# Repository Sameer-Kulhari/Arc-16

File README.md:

# Arc-16

Arc-16 is a macro-pad with 16 keys,oled and rgb for aesthetics and look ,with a custom cool looking 3d case and working on kmk firmware .

## Features :
- 16 keys 
- Oled (128*32)
- Rgb under keys 
- kmk firmware
- 3 layers for rgb and functions control keys

## CAD :
#### Here are some looks of Arc-16 .

It has two parts top and bottom which can be assembled using M3 screws and heatsets.The design is made in Onshape.

### Full Case 

### Bottom

## PCB :
#### Here are some looks of PCB

This pcb is made in kicad.
### 3d view

### Schematics

## Firmware 
### Arc -16 uses kmk Firmware with Circuit-python

- 3 layers for more keys
- Oled displays current layer
- Rgb with different modes

## BOM 
Here is a list of materials required to make the Arc-16

- 1x Seeed XIAO RP2040
- 16x Cherry MX 1.0u Switches
- 1x 0.91 inch OLED display
- 9x SK6812 mini-e LEDs
- 16x 1N14148 diodes
- Pcb of Arc-16
- Case of Arc-16
- 4x M3 screws
- 4x M3 heatsets
- 16x Blank DSA keycaps

## Extra 

### All images are attached in each section along with dependancies.Have a look at it.
####  _________________Thank You!____________________

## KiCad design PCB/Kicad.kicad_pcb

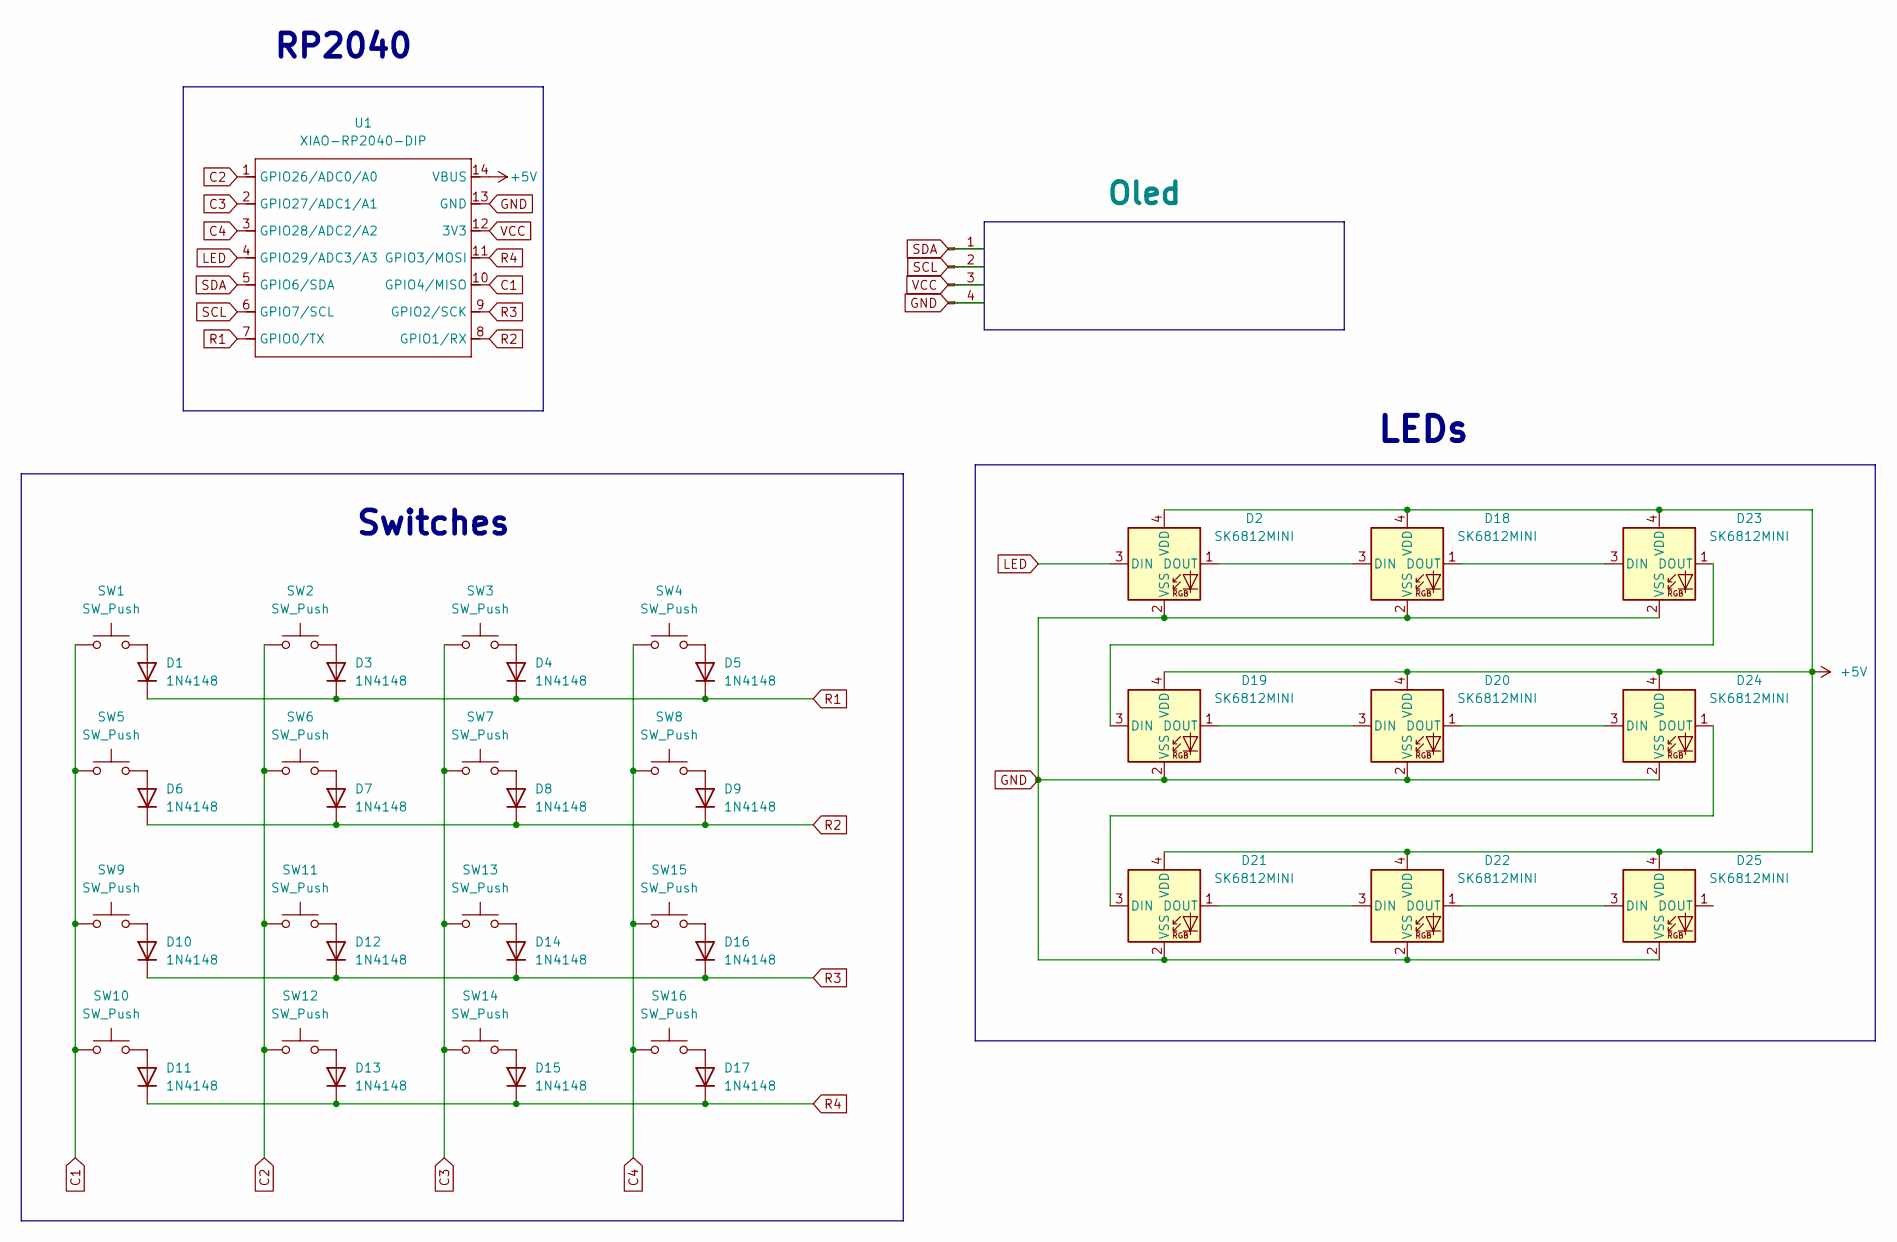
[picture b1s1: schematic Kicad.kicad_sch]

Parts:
D1, D3, D4, D5, D6, D7, D8, D9, D10, D11, D12, D13, D14, D15, D16, D17: 1N4148; D_DO-35_SOD27_P7.62mm_Horizontal
D2, D18, D19, D20, D21, D22, D23, D24, D25: SK6812MINI; SK6812-MINI-E
J1: Oled; PinHeader_1x04_P2.54mm_Vertical
SW1, SW2, SW3, SW4, SW5, SW6, SW7, SW8, SW9, SW10, SW11, SW12, SW13, SW14, SW15, SW16: SW_Push; SW_Cherry_MX_1.00u_PCB_With_3d
U1: XIAO-RP2040-DIP

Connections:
+5V: D2.4 (VDD), D18.4 (VDD), D19.4 (VDD), D20.4 (VDD), D21.4 (VDD), D22.4 (VDD), D23.4 (VDD), D24.4 (VDD), D25.4 (VDD), U1.14 (VBUS)
C1: SW1.1, SW5.1, SW9.1, SW10.1, U1.10 (GPIO4/MISO)
C2: SW2.1, SW6.1, SW11.1, SW12.1, U1.1 (GPIO26/ADC0/A0)
C3: SW3.1, SW7.1, SW13.1, SW14.1, U1.2 (GPIO27/ADC1/A1)
C4: SW4.1, SW8.1, SW15.1, SW16.1, U1.3 (GPIO28/ADC2/A2)
GND: D2.2 (VSS), D18.2 (VSS), D19.2 (VSS), D20.2 (VSS), D21.2 (VSS), D22.2 (VSS), D23.2 (VSS), D24.2 (VSS), D25.2 (VSS), J1.4, U1.13 (GND)
LED: D2.3 (DIN), U1.4 (GPIO29/ADC3/A3)
unnamed: D1.2 (A), SW1.2
unnamed: D3.2 (A), SW2.2
unnamed: D4.2 (A), SW3.2
unnamed: D5.2 (A), SW4.2
unnamed: D6.2 (A), SW5.2
unnamed: D7.2 (A), SW6.2
unnamed: D8.2 (A), SW7.2
unnamed: D9.2 (A), SW8.2
unnamed: D10.2 (A), SW9.2
unnamed: D11.2 (A), SW10.2
unnamed: D12.2 (A), SW11.2
unnamed: D13.2 (A), SW12.2
unnamed: D14.2 (A), SW13.2
unnamed: D15.2 (A), SW14.2
unnamed: D16.2 (A), SW15.2
unnamed: D17.2 (A), SW16.2
unnamed: D2.1 (DOUT), D18.3 (DIN)
unnamed: D18.1 (DOUT), D23.3 (DIN)
unnamed: D19.3 (DIN), D23.1 (DOUT)
unnamed: D19.1 (DOUT), D20.3 (DIN)
unnamed: D20.1 (DOUT), D24.3 (DIN)
unnamed: D21.3 (DIN), D24.1 (DOUT)
unnamed: D21.1 (DOUT), D22.3 (DIN)
unnamed: D22.1 (DOUT), D25.3 (DIN)
R1: D1.1 (K), D3.1 (K), D4.1 (K), D5.1 (K), U1.7 (GPIO0/TX)
R2: D6.1 (K), D7.1 (K), D8.1 (K), D9.1 (K), U1.8 (GPIO1/RX)
R3: D10.1 (K), D12.1 (K), D14.1 (K), D16.1 (K), U1.9 (GPIO2/SCK)
R4: D11.1 (K), D13.1 (K), D15.1 (K), D17.1 (K), U1.11 (GPIO3/MOSI)
SCL: J1.2, U1.6 (GPIO7/SCL)
SDA: J1.1, U1.5 (GPIO6/SDA)
VCC: J1.3, U1.12 (3V3)

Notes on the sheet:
LEDs
Switches
RP2040

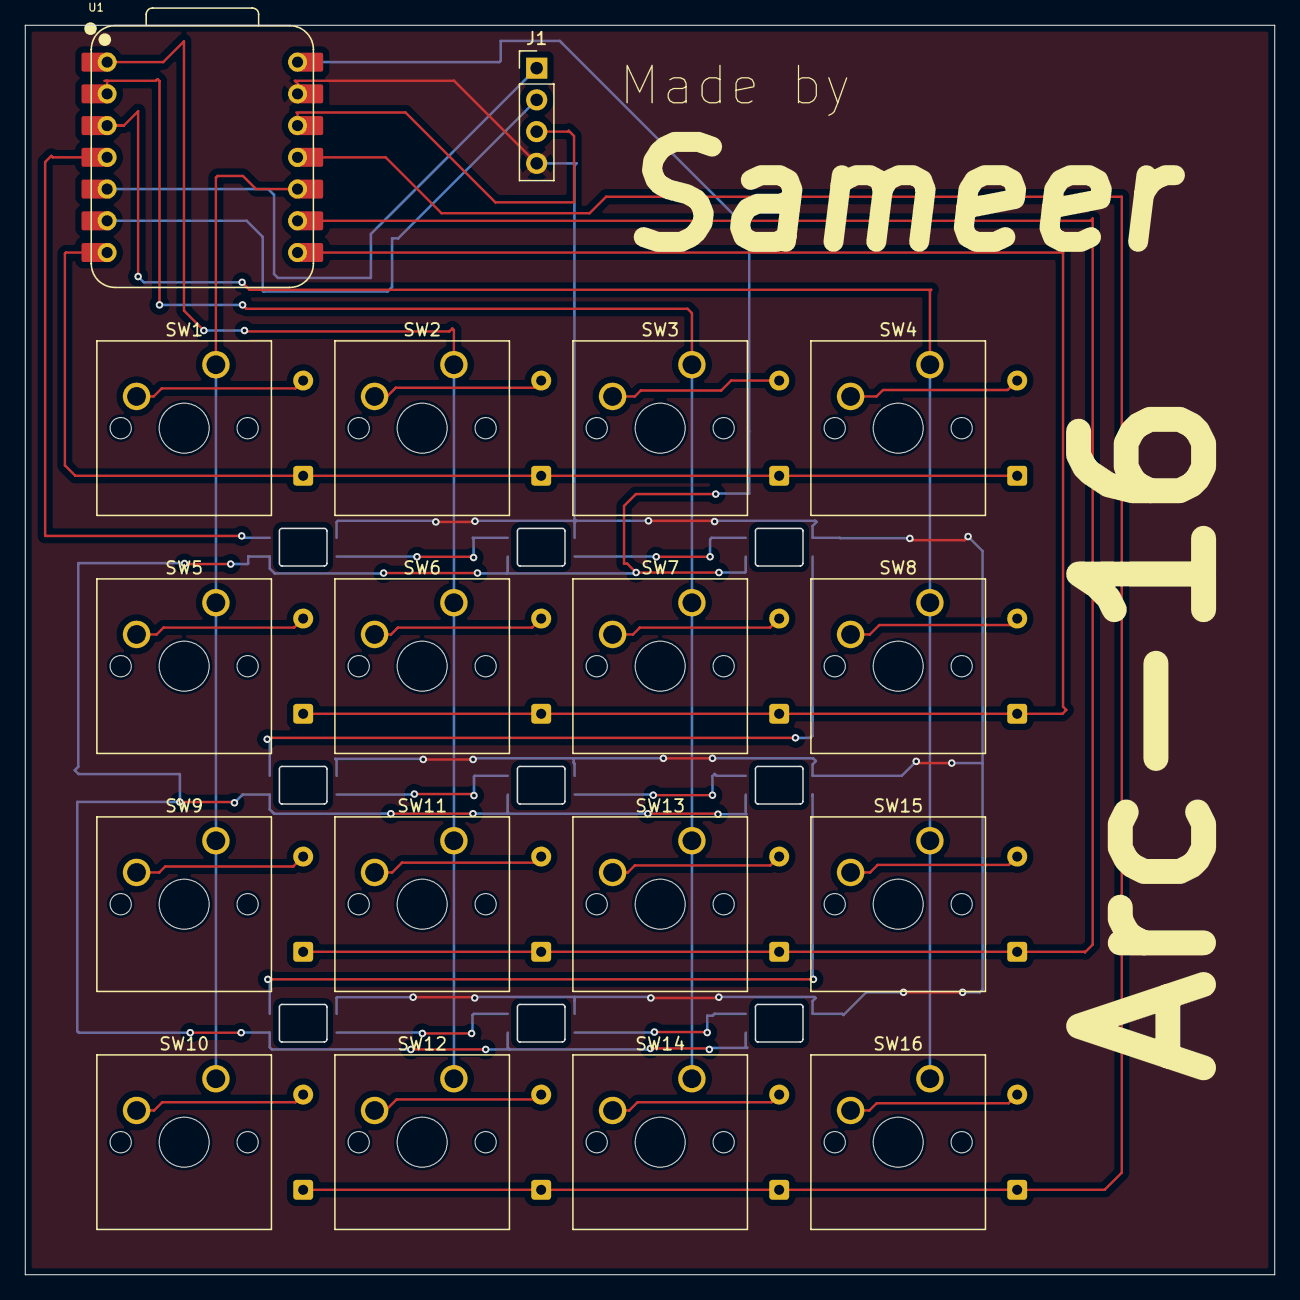
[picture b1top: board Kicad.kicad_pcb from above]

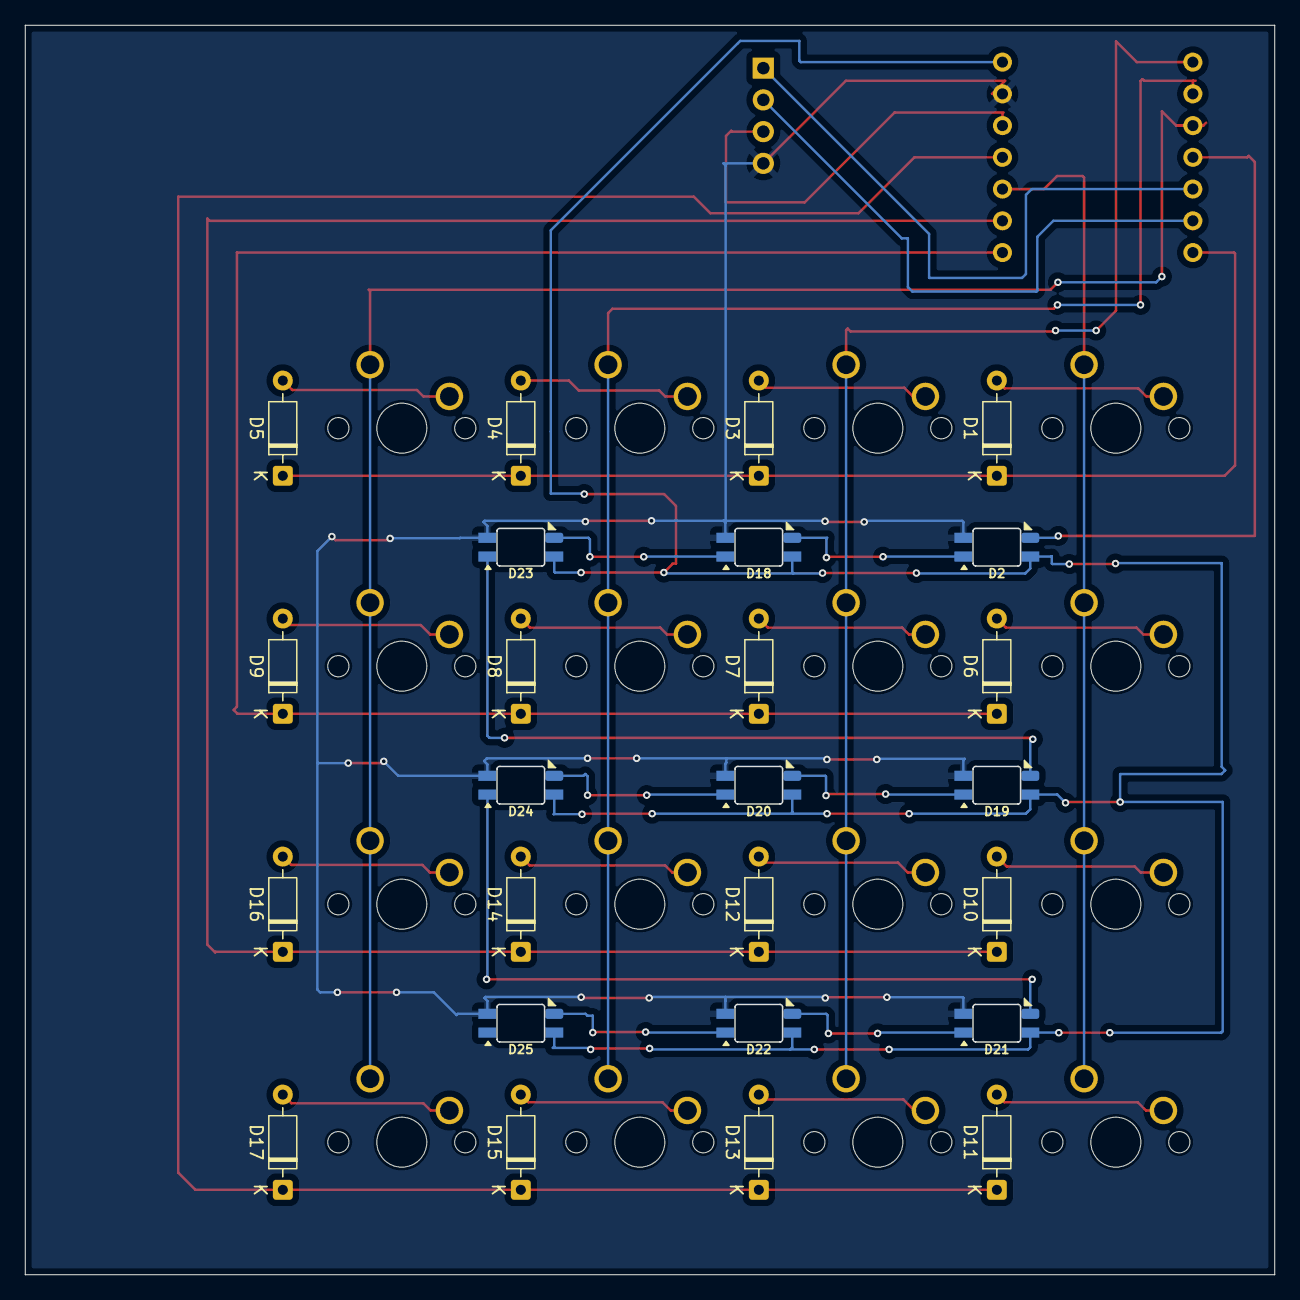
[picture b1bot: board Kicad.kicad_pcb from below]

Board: 2 copper layers, 99.9 x 99.9 mm, 43 parts (25 on the bottom side), 38 nets.

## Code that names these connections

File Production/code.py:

import board
from kmk.kmk_keyboard import KMKKeyboard
from kmk.scanners import MatrixScanner
from kmk.keys import KC
from kmk.modules.layers import Layers
from kmk.modules.rgb import RGB 
from kmk.extensions.display import Display
from kmk.extensions.display.display_oled import DisplayOLED 
from adafruit_display_text.label import Label
import terminalio


keyboard = KMKKeyboard()


keyboard.col_pins = (board.GPIO4, board.GPIO26, board.GPIO27, board.GPIO28)
keyboard.row_pins = (board.GPIO0, board.GPIO1, board.GPIO2, board.GPIO3)
keyboard.diode_orientation = MatrixScanner.DIODE_COL2ROW


keyboard.modules.append(Layers())


rgb = RGB(
    pixel_pin=board.GPIO29,
    num_pixels=9,
    rgb_order=(1, 0, 2),  # GRB
    brightness_limit=64,
    animation_speed=2.0,
)
rgb.default_rgb_effect = rgb.RGB_MODE_BREATHE_RAINBOW
keyboard.modules.append(rgb)


oled = DisplayOLED(
    width=128,
    height=32,
    sda=board.SDA,
    scl=board.SCL,
    addr=0x3C,
    rotate=0,
)
display = Display(oled)

# OLED for showing current layer name
def draw_oled(display_inst, keyboard):
    current_layer = keyboard.active_layers[0] if keyboard.active_layers else 0
    layer_names = ['Base', 'Fn', 'RGB']
    name = layer_names[current_layer] if current_layer < len(layer_names) else f'Layer {current_layer}'

    display_inst.clear_display_group()
    label = Label(terminalio.FONT, text=f'Layer: {name}', x=0, y=8)
    display_inst.display_group.append(label)

display.draw_callback = draw_oled
keyboard.extensions.append(display)



LAYER_FN = KC.TG(1)   
LAYER_RGB = KC.TG(2)  
LAYER_BASE = KC.TG(0) 

# Keymap
keyboard.keymap = [

    # Layer 0: Base
    [
        KC.ESC,  KC.Q,    KC.W,    KC.E,
        KC.A,    KC.S,    KC.D,    KC.F,
        KC.Z,    KC.X,    KC.C,    KC.V,
        LAYER_FN, KC.SPC, KC.ENT,  KC.BSPC,
    ],

    # Layer 1: Function Layer
    [
        KC.TILD, KC.N1,   KC.N2,   KC.N3,
        KC.N4,   KC.N5,   KC.N6,   KC.N7,
        KC.N8,   KC.N9,   KC.N0,   KC.MINS,
        LAYER_RGB, KC.LEFT, KC.DOWN, KC.RIGHT,
    ],

    # Layer 2: RGB Controls
    [
        KC.RGB_TOG, KC.RGB_MOD, KC.RGB_HUI, KC.RGB_HUD,
        KC.RGB_VAI, KC.RGB_VAD, KC.NO,      KC.NO,
        KC.NO,      KC.NO,      KC.NO,      KC.NO,
        LAYER_BASE,    KC.TRNS,    KC.TRNS,    KC.TRNS,
    ]
]

if __name__ == '__main__':
    keyboard.go()

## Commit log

2025-06-28 Create a new directory
2025-06-28 Added Kicad files
2025-06-28 Create a library folder
2025-06-28 Added footprint for project
2025-06-28 Create folder
2025-06-28 Create Libraries
2025-06-29 Added images
2025-06-29 Plate Design added
2025-06-29 Added main.py
2025-06-29 Added CAD files
2025-06-29 Added new files
2025-06-30 added firmware files
